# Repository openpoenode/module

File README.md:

# Technical Specifications

## Core Components

| Component              |                                  |
|------------------------|----------------------------------|
| MCU                    | ESP32-D0WD-V3                    |
| Flash                  | Winbond SPI 128MBit W25Q128JVP   |
| RAM                    | APMemory 64MBit APS6404L-3SQR-SN |
| Ethernet PHY           | SMSC LAN8720A                    |
| PoE 802.3af Controller | TI TPS23753                      |
| eFuse                  | TI TPS259520DSGR                 |

### Flash Memory

Any standard, pin-compatible SPI NOR flash in a WSON-8 6x5 mm package can be used. Common options are the 32MBit and 64MBit chips from the same line of Winbond flash memories.

### PSRAM

Installing a PSRAM chip is optional, the module will work just fine without the PSRAM IC populated. While any pin-compatible PSRAM chip can be installed, any amount over 32Mbit cannot be addressed by the ESP32 MCU.

### eFuse

- The digital power domain (MCU power supply input) is protected by a latch-off type eFuse. It disconnects supply at V<sub>in</sub> > 3.8V or I<sub>in</sub> > 1.04A.
- The module exposes a test pad for measuring the supply current drawn by the module's digital domain components:
  - I<sub>in</sub> = 1.81 x V<sub>test</sub>
  - V<sub>test</sub> is measured against digital ground

## Goldfinger Connector

The module exposes several signals of its components through a goldfinger connector:

### GPIOs

| GPIO | free | limited | input-only |
|------|------|---------|------------|
| 2    |      | X       |            |
| 4    |      | X       |            |
| 5    |      | X       |            |
| 12   |      | X       |            |
| 13   | X    |         |            |
| 14   | X    |         |            |
| 15   |      | X       |            |
| 18   | X    |         |            |
| 23   | X    |         |            |
| 32   | X    |         |            |
| 33   | X    |         |            |
| 34   |      |         | X          |
| 35   |      |         | X          |
| 36   |      |         | X          |
| 37   |      |         | X          |
| 38   |      |         | X          |
| 39   |      |         | X          |

GPIOs marked as "limited" have a boot-strapping function and/or a fixed pull-up/pull-down in place.

3 output-capable GPIOs have to be assigned for Ethernet PHY control.

### Ethernet Interface

- Analog (2 differential data pairs, 2x center taps power input)
- 2 Indicator LEDs (Link/Activity, Speed)
- Bob-Smith-Termination
- Digital interface (Enable/Reset, MDC, MDIO)

### Power Supply / Conversion

- High Voltage (PoE domain)
  - External power adapter input, 36V < V<sub>in</sub> < 54V
  - Direct PoE power output for additional DC/DC converters (maximum power draw limited to 802.3af level)
- Low Voltage (Isolated domain)
  - DC/DC converter V<sub>out</sub> = 5V (3.3V optional)
  - I<sub>out,max</sub> = 1.4A (5V) or 2.1A (3.3V)
  - 7W max. output
- Digital domain
  - MCU power supply input (external 3.3V supply required)
  - I<sub>supply,avg</sub> < 500mA (soft limit)
  - I<sub>supply,lim</sub> = 1.04A (latch-off limit)
  - I<sub>supply,idle</sub> = ~150mA (idle supply current - including flash, RAM, 100MBit connected Ethernet, Link/Speed indicators on)

### Programming Interface

- ESP32 UART
- MCU Reset
- GPIO0 (boot strapping only, no direct connection)

## Physical

- Standard Mini-PCIe goldfinger connector, 52 pins
- FR4 1.00 mm base material, 6 layers
- Size: 45 x 30 x 14.5 mm
- Weight: 12g

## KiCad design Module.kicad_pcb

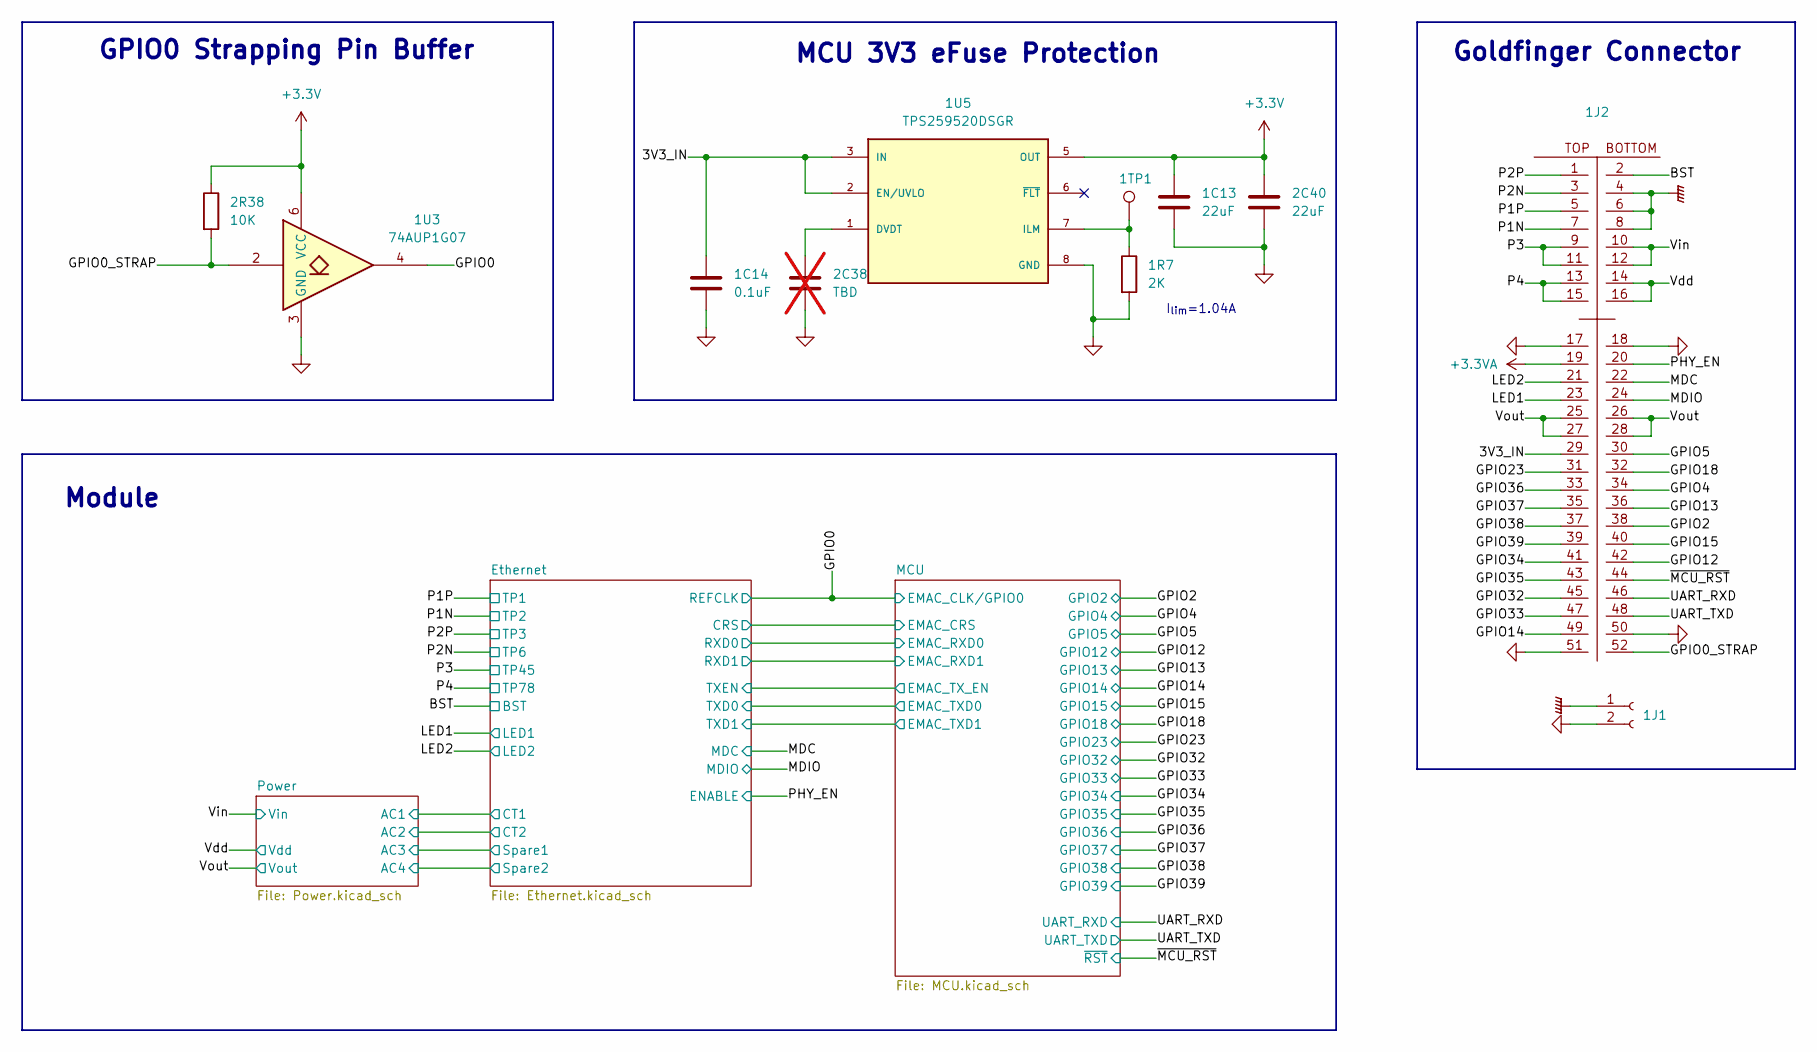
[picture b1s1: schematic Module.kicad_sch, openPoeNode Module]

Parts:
1C13, 2C40: 22uF; C_0805_2012Metric; MOUSER# 81-GRM21BZ71A226ME5L
1C14: 0.1uF; C_0402_1005Metric; MOUSER# 81-GCM155R71H104KE2J
1J1: HOLDDOWN; mPCIe-Hold
1J2: Mini-PCIe
1R7: 2K; R_0402_1005Metric; MOUSER# 71-CRCW0402-2.0K-E3
1TP1: TestPoint; TestPoint_Pad_D2.0mm
1U3: 74AUP1G07; Texas_USON-6_1x1.45mm_P0.5mm_SMD; MOUSER# 595-SN74AUP1G07DRYR
1U5: TPS259520DSGR; SON50P200X200X80-9N; MOUSER# 595-TPS259520DSGR
2C38: TBD; C_0402_1005Metric; not fitted
2R38: 10K; R_0402_1005Metric; MOUSER# 603-RE0402FRE0710KL

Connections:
+3.3V: 1C13.1, 1U3.6 (VCC), 1U5.5 (OUT), 2C40.1, 2R38.1; also elsewhere on the board
+3.3VA: 1J2.19; also elsewhere on the board
/3V3_IN: 1C14.2, 1J2.29, 1U5.2 (EN/UVLO), 1U5.3 (IN), 1U5.4 (IN)
/BST: 1J2.2; also elsewhere on the board
/GPIO0: 1U3.4; also elsewhere on the board
/GPIO0_STRAP: 1J2.52, 1U3.2, 2R38.2
/GPIO2: 1J2.38; also elsewhere on the board
/GPIO4: 1J2.34; also elsewhere on the board
/GPIO5: 1J2.30; also elsewhere on the board
/GPIO12: 1J2.42; also elsewhere on the board
/GPIO13: 1J2.36; also elsewhere on the board
/GPIO14: 1J2.49; also elsewhere on the board
/GPIO15: 1J2.40; also elsewhere on the board
/GPIO18: 1J2.32; also elsewhere on the board
/GPIO23: 1J2.31; also elsewhere on the board
/GPIO32: 1J2.45; also elsewhere on the board
/GPIO33: 1J2.47; also elsewhere on the board
/GPIO34: 1J2.41; also elsewhere on the board
/GPIO35: 1J2.43; also elsewhere on the board
/GPIO36: 1J2.33; also elsewhere on the board
/GPIO37: 1J2.35; also elsewhere on the board
/GPIO38: 1J2.37; also elsewhere on the board
/GPIO39: 1J2.39; also elsewhere on the board
/LED1: 1J2.23; also elsewhere on the board
/LED2: 1J2.21; also elsewhere on the board
/MDC: 1J2.22; also elsewhere on the board
/MDIO: 1J2.24; also elsewhere on the board
/P1N: 1J2.7; also elsewhere on the board
/P1P: 1J2.5; also elsewhere on the board
/P2N: 1J2.3; also elsewhere on the board
/P2P: 1J2.1; also elsewhere on the board
/P3: 1J2.9, 1J2.11; also elsewhere on the board
/P4: 1J2.13, 1J2.15; also elsewhere on the board
/PHY_EN: 1J2.20; also elsewhere on the board
/UART_RXD: 1J2.46; also elsewhere on the board
/UART_TXD: 1J2.48; also elsewhere on the board
/Vdd: 1J2.14, 1J2.16; also elsewhere on the board
/Vin: 1J2.10, 1J2.12; also elsewhere on the board
/Vout: 1J2.25, 1J2.26, 1J2.27, 1J2.28; also elsewhere on the board
/~MCU_RST: 1J2.44; also elsewhere on the board
GND: 1C13.2, 1C14.1, 1J1.2, 1J2.17, 1J2.18, 1J2.50, 1J2.51, 1R7.2, 1U3.3 (GND), 1U5.8 (GND), 1U5.9 (GND), 2C38.2, 2C40.2; also elsewhere on the board
GNDPWR: 1J1.1, 1J2.4, 1J2.6, 1J2.8; also elsewhere on the board
unnamed: 1U5.1 (DVDT), 2C38.1
unnamed: 1R7.1, 1TP1.1, 1U5.7 (ILM)

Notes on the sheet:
Goldfinger Connector
I_{lim}=1.04A
MCU 3V3 eFuse Protection
GPIO0 Strapping Pin Buffer
Module

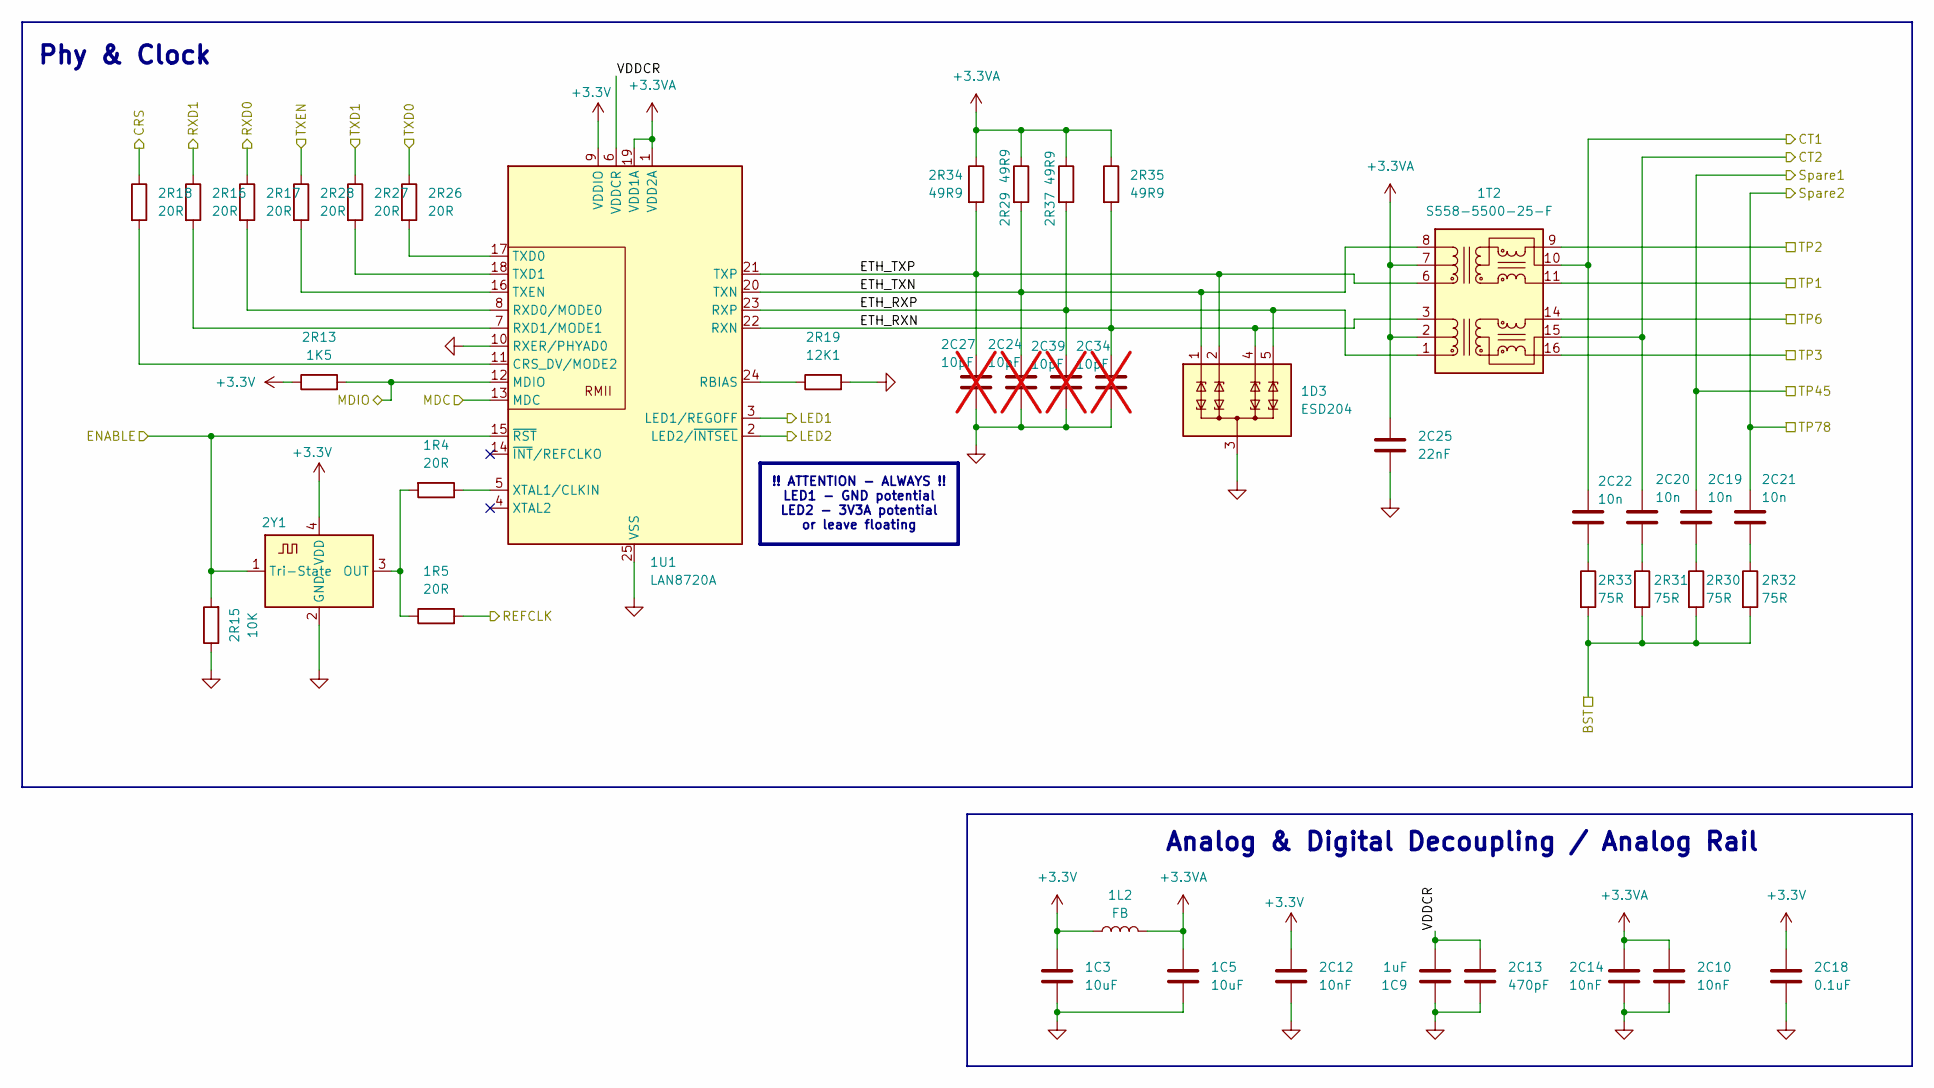
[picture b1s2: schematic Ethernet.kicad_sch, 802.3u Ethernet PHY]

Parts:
1C3, 1C5: 10uF; C_0805_2012Metric; MOUSER# 81-GRM21BR71A106MA3L
1C9: 1uF; C_0603_1608Metric; MOUSER# 963-EMK107B7105KA-T
1D3: ESD204; USON-10_2.5x1.0mm_P0.5mm; MOUSER# 595-ESD204DQAR
1L2: FB; L_0805_2012Metric; MOUSER#(alt) 603-BBPY201209121Y00
1R4, 1R5, 2R16, 2R17, 2R18, 2R26, 2R27, 2R28: 20R; R_0402_1005Metric; MOUSER# 660-RK73B1ETTP200J
1T2: S558-5500-25-F; MOUSER# 530-S558-5500-25-F
1U1: LAN8720A; QFN-24-1EP_4x4mm_P0.5mm_EP2.5x2.5mm; MOUSER# 579-LAN8720ACPTRABC
2C10, 2C12, 2C14: 10nF; C_0402_1005Metric; MOUSER# 963-EMK105B7103KV-F
2C13: 470pF; C_0402_1005Metric; MOUSER# 791-0402B471K250CT
2C18: 0.1uF; C_0402_1005Metric; MOUSER# 81-GCM155R71H104KE2J
2C19, 2C20, 2C21, 2C22: 10n; C_0603_1608Metric; MOUSER# 603-CC0603JRX70BB103
2C24, 2C27, 2C34, 2C39: 10pF; C_0402_1005Metric; MOUSER# 963-UMK105CG100DV-F; not fitted
2C25: 22nF; C_0402_1005Metric; MOUSER# 81-GRM155R71H223KA2J
2R13: 1K5; R_0402_1005Metric; MOUSER# 667-ERJ-2RKF1501X
2R15: 10K; R_0402_1005Metric; MOUSER# 603-RE0402FRE0710KL
2R19: 12K1; R_0402_1005Metric; MOUSER# 603-RT0402FRE0712K1L
2R29, 2R34, 2R35, 2R37: 49R9; R_0402_1005Metric; MOUSER# 660-RK73H1ETTP49R9F
2R30, 2R31, 2R32, 2R33: 75R; R_0603_1608Metric; MOUSER# 660-SG73S1JTTD75R0F
2Y1: ECS-2333-500-BN-TR; Crystal_SMD_3225-4Pin_3.2x2.5mm; MOUSER# 520-ECS-2333-500-BNT

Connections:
+3.3V: 1C3.1, 1L2.1, 1U1.9 (VDDIO), 2C12.2, 2C18.2, 2R13.1, 2Y1.4 (VDD); also elsewhere on the board
+3.3VA: 1C5.1, 1L2.2, 1T2.2 (C_TD), 1T2.7 (C_RD), 1U1.1 (VDD2A), 1U1.19 (VDD1A), 2C10.2, 2C14.2, 2C25.1, 2R29.1, 2R34.1, 2R35.1, 2R37.1; also elsewhere on the board
/BST: 2R30.2, 2R31.2, 2R32.2, 2R33.2; also elsewhere on the board
/Ethernet/CRS: 2R18.1; also elsewhere on the board
/Ethernet/CT1: 1T2.10 (C_RX), 2C22.1; also elsewhere on the board
/Ethernet/CT2: 1T2.15 (C_TX), 2C20.1; also elsewhere on the board
/Ethernet/ETH_RXN: 1D3.4 (TVS3), 1D3.7 (TVS3), 1T2.3 (TD-), 1U1.22 (RXN), 2C34.1, 2R35.2
/Ethernet/ETH_RXP: 1D3.5 (TVS4), 1D3.6 (TVS4), 1T2.1 (TD+), 1U1.23 (RXP), 2C39.1, 2R37.2
/Ethernet/ETH_TXN: 1D3.1 (TVS1), 1D3.10 (TVS1), 1T2.8 (RD-), 1U1.20 (TXN), 2C24.1, 2R29.2
/Ethernet/ETH_TXP: 1D3.2 (TVS2), 1D3.9 (TVS2), 1T2.6 (RD+), 1U1.21 (TXP), 2C27.1, 2R34.2
/Ethernet/RXD0: 2R17.1; also elsewhere on the board
/Ethernet/RXD1: 2R16.1; also elsewhere on the board
/Ethernet/TXD0: 2R26.1; also elsewhere on the board
/Ethernet/TXD1: 2R27.1; also elsewhere on the board
/Ethernet/TXEN: 2R28.1; also elsewhere on the board
/Ethernet/VDDCR: 1C9.1, 1U1.6 (VDDCR), 2C13.1
/GPIO0: 1R5.2; also elsewhere on the board
/LED1: 1U1.3 (LED1/REGOFF); also elsewhere on the board
/LED2: 1U1.2 (LED2/~INTSEL); also elsewhere on the board
/MDC: 1U1.13 (MDC); also elsewhere on the board
/MDIO: 1U1.12 (MDIO), 2R13.2; also elsewhere on the board
/P1N: 1T2.9 (RX-); also elsewhere on the board
/P1P: 1T2.11 (RX+); also elsewhere on the board
/P2N: 1T2.14 (TX-); also elsewhere on the board
/P2P: 1T2.16 (TX+); also elsewhere on the board
/P3: 2C19.1; also elsewhere on the board
/P4: 2C21.1; also elsewhere on the board
/PHY_EN: 1U1.15 (~RST), 2R15.2, 2Y1.1 (Tri-State); also elsewhere on the board
GND: 1C3.2, 1C5.2, 1C9.2, 1D3.3 (COM), 1D3.8 (COM), 1U1.10 (RXER/PHYAD0), 1U1.25 (VSS), 2C10.1, 2C12.1, 2C13.2, 2C14.1, 2C18.1, 2C24.2, 2C25.2, 2C27.2, 2C34.2, 2C39.2, 2R15.1, 2R19.2, 2Y1.2 (GND); also elsewhere on the board
unnamed: 1U1.11 (CRS_DV/MODE2), 2R18.2
unnamed: 1U1.24 (RBIAS), 2R19.1
unnamed: 1U1.8 (RXD0/MODE0), 2R17.2
unnamed: 1U1.7 (RXD1/MODE1), 2R16.2
unnamed: 1U1.17 (TXD0), 2R26.2
unnamed: 1U1.18 (TXD1), 2R27.2
unnamed: 1U1.16 (TXEN), 2R28.2
unnamed: 1R4.1, 1U1.5 (XTAL1/CLKIN)
unnamed: 2C19.2, 2R30.1
unnamed: 2C20.2, 2R31.1
unnamed: 2C21.2, 2R32.1
unnamed: 2C22.2, 2R33.1
unnamed: 1R4.2, 1R5.1, 2Y1.3 (OUT)

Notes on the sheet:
Phy & Clock
!! ATTENTION - ALWAYS !! LED1 - GND potential LED2 - 3V3A potential or leave floating
Analog & Digital Decoupling / Analog Rail

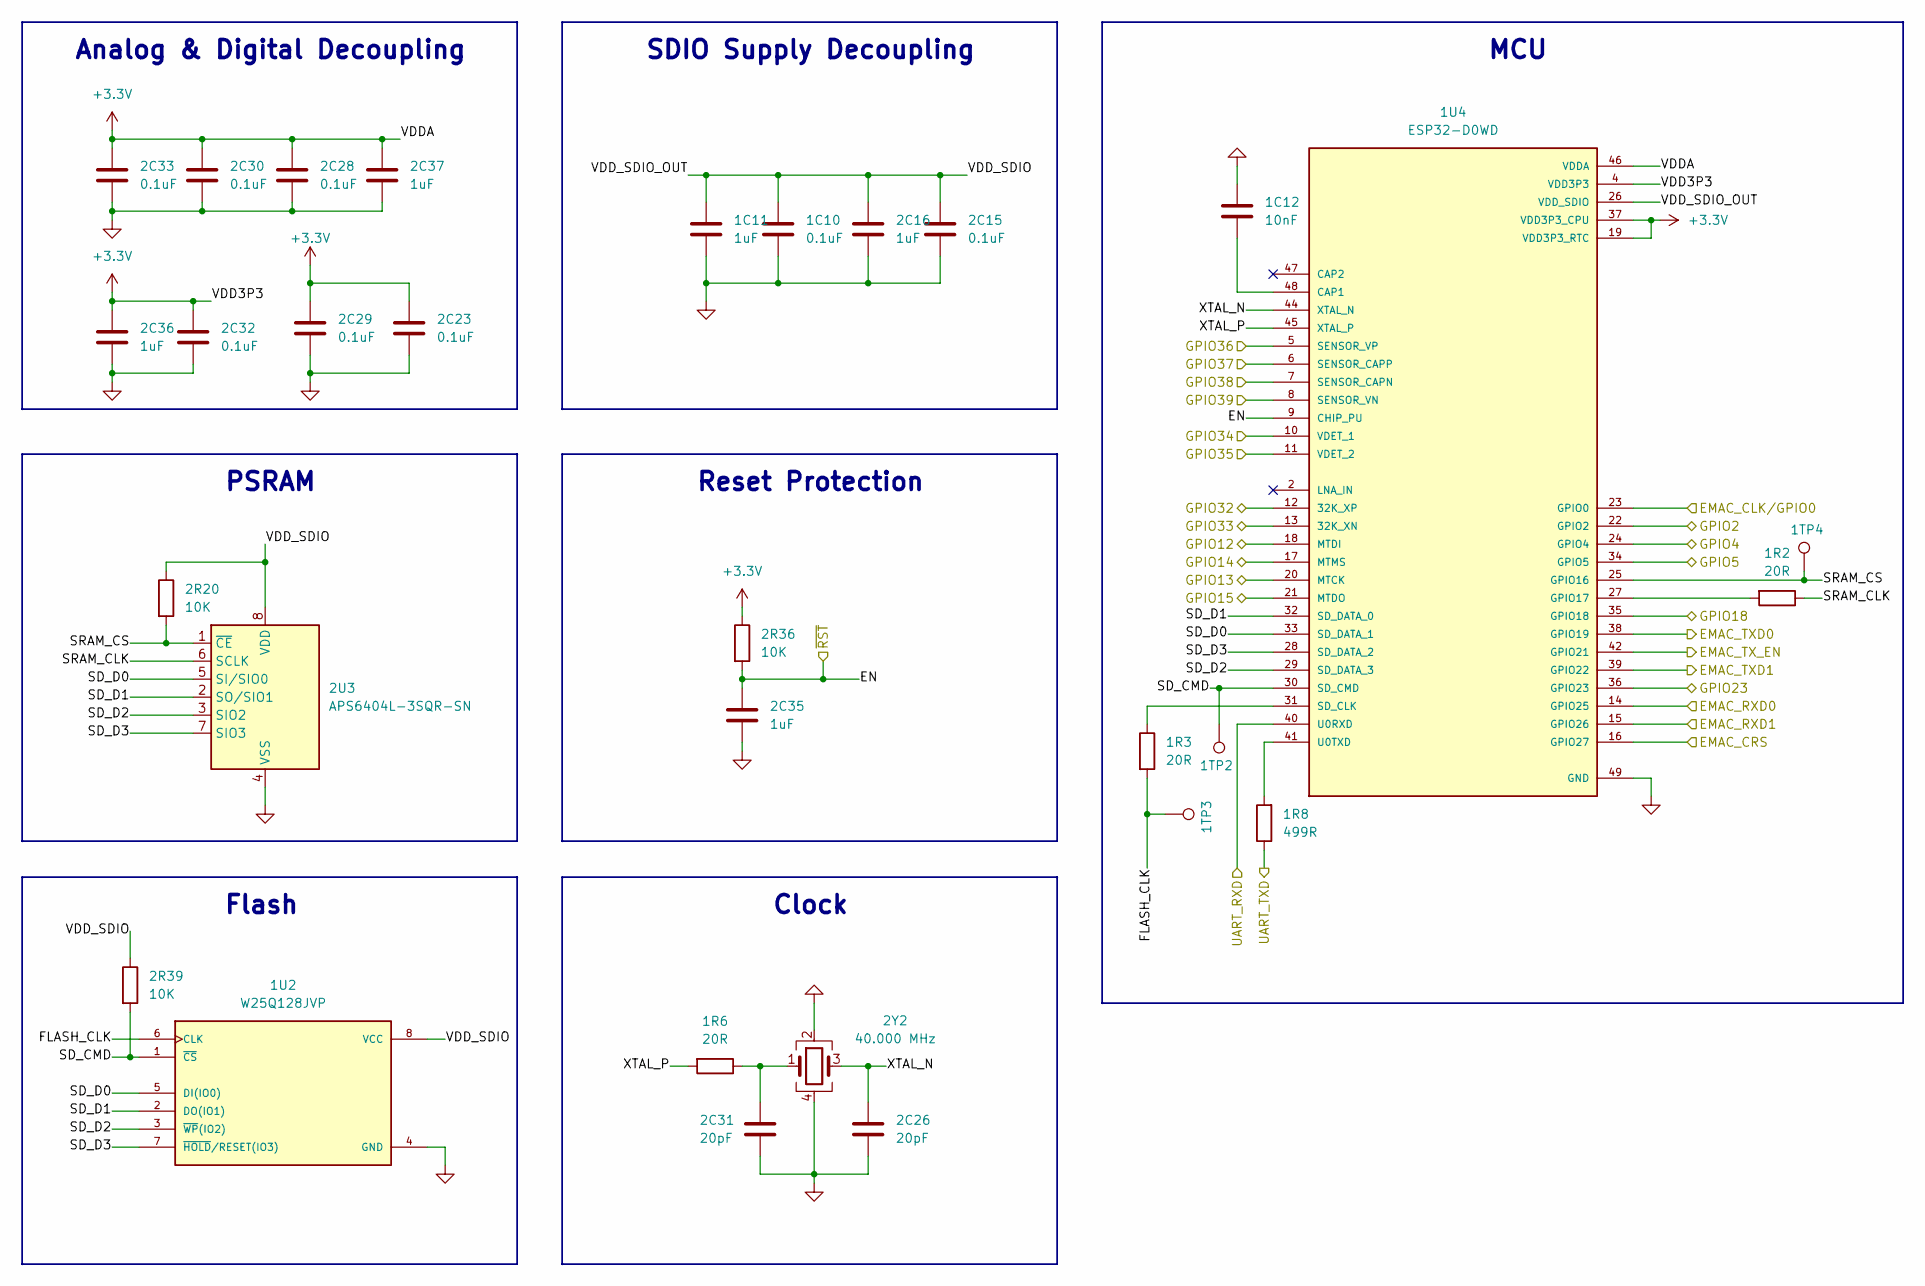
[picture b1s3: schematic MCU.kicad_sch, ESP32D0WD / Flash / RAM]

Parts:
1C10, 2C15, 2C23, 2C28, 2C29, 2C30, 2C32, 2C33: 0.1uF; C_0402_1005Metric; MOUSER# 81-GCM155R71H104KE2J
1C11, 2C16, 2C35, 2C36, 2C37: 1uF; C_0603_1608Metric; MOUSER# 963-EMK107B7105KA-T
1C12: 10nF; C_0402_1005Metric; MOUSER# 963-EMK105B7103KV-F
1R2, 1R3, 1R6: 20R; R_0402_1005Metric; MOUSER# 660-RK73B1ETTP200J
1R8: 499R; R_0402_1005Metric; MOUSER# 791-RMC1/16SK4990FTH
1TP2, 1TP3, 1TP4: TestPoint; TestPoint_Pad_D1.0mm
1U2: W25Q128JVP; SON127P600X500X80-9N; MOUSER# 454-W25Q128JVPIM
1U4: ESP32-D0WD; QFN-48-1EP_5x5mm_P0.35mm_EP3.7x3.7mm; MOUSER# 356-ESP32-D0WD-V3
2C26, 2C31: 20pF; C_0402_1005Metric; MOUSER# 187-CL05C200JB51PNC
2R20, 2R36, 2R39: 10K; R_0402_1005Metric; MOUSER# 603-RE0402FRE0710KL
2U3: APS6404L-3SQR-SN; SOIC-8_3.9x4.9mm_P1.27mm; MOUSER# 878-APS6404L-3SQR-SN
2Y2: 40.000 MHz; Crystal_SMD_3225-4Pin_3.2x2.5mm; MOUSER# 815-M840000MHZ12B1UT

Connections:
+3.3V: 1U4.1 (VDDA), 1U4.3 (VDD3P3), 1U4.4 (VDD3P3), 1U4.19 (VDD3P3_RTC), 1U4.37 (VDD3P3_CPU), 1U4.43 (VDDA), 1U4.46 (VDDA), 2C23.2, 2C28.2, 2C29.2, 2C30.2, 2C32.2, 2C33.2, 2C36.2, 2C37.2, 2R36.1; also elsewhere on the board
/Ethernet/CRS: 1U4.16 (GPIO27); also elsewhere on the board
/Ethernet/RXD0: 1U4.14 (GPIO25); also elsewhere on the board
/Ethernet/RXD1: 1U4.15 (GPIO26); also elsewhere on the board
/Ethernet/TXD0: 1U4.38 (GPIO19); also elsewhere on the board
/Ethernet/TXD1: 1U4.39 (GPIO22); also elsewhere on the board
/Ethernet/TXEN: 1U4.42 (GPIO21); also elsewhere on the board
/GPIO0: 1U4.23 (GPIO0); also elsewhere on the board
/GPIO2: 1U4.22 (GPIO2); also elsewhere on the board
/GPIO4: 1U4.24 (GPIO4); also elsewhere on the board
/GPIO5: 1U4.34 (GPIO5); also elsewhere on the board
/GPIO12: 1U4.18 (MTDI); also elsewhere on the board
/GPIO13: 1U4.20 (MTCK); also elsewhere on the board
/GPIO14: 1U4.17 (MTMS); also elsewhere on the board
/GPIO15: 1U4.21 (MTDO); also elsewhere on the board
/GPIO18: 1U4.35 (GPIO18); also elsewhere on the board
/GPIO23: 1U4.36 (GPIO23); also elsewhere on the board
/GPIO32: 1U4.12 (32K_XP); also elsewhere on the board
/GPIO33: 1U4.13 (32K_XN); also elsewhere on the board
/GPIO34: 1U4.10 (VDET_1); also elsewhere on the board
/GPIO35: 1U4.11 (VDET_2); also elsewhere on the board
/GPIO36: 1U4.5 (SENSOR_VP); also elsewhere on the board
/GPIO37: 1U4.6 (SENSOR_CAPP); also elsewhere on the board
/GPIO38: 1U4.7 (SENSOR_CAPN); also elsewhere on the board
/GPIO39: 1U4.8 (SENSOR_VN); also elsewhere on the board
/MCU/FLASH_CLK: 1R3.2, 1TP3.1, 1U2.6 (CLK)
/MCU/SD_CMD: 1TP2.1, 1U2.1 (~CS), 1U4.30 (SD_CMD), 2R39.2
/MCU/SD_D0: 1U2.5 (DI(IO0)), 1U4.33 (SD_DATA_1), 2U3.5 (SI/SIO0)
/MCU/SD_D1: 1U2.2 (DO(IO1)), 1U4.32 (SD_DATA_0), 2U3.2 (SO/SIO1)
/MCU/SD_D2: 1U2.3 (~WP(IO2)), 1U4.29 (SD_DATA_3), 2U3.3 (SIO2)
/MCU/SD_D3: 1U2.7 (~HOLD/RESET(IO3)), 1U4.28 (SD_DATA_2), 2U3.7 (SIO3)
/MCU/SRAM_CLK: 1R2.1, 2U3.6 (SCLK)
/MCU/SRAM_CS: 1TP4.1, 1U4.25 (GPIO16), 2R20.2, 2U3.1 (~CE)
/MCU/VDD_SDIO: 1C10.2, 1C11.2, 1U2.8 (VCC), 1U4.26 (VDD_SDIO), 2C15.2, 2C16.2, 2R20.1, 2R39.1, 2U3.8 (VDD)
/MCU/XTAL_N: 1U4.44 (XTAL_N), 2C26.1, 2Y2.3
/MCU/XTAL_P: 1R6.2, 1U4.45 (XTAL_P)
/UART_RXD: 1U4.40 (U0RXD); also elsewhere on the board
/UART_TXD: 1R8.1; also elsewhere on the board
/~MCU_RST: 1U4.9 (CHIP_PU), 2C35.2, 2R36.2; also elsewhere on the board
GND: 1C10.1, 1C11.1, 1C12.2, 1U2.4 (GND), 1U4.49 (GND), 2C15.1, 2C16.1, 2C23.1, 2C26.2, 2C28.1, 2C29.1, 2C30.1, 2C31.2, 2C32.1, 2C33.1, 2C35.1, 2C36.1, 2C37.1, 2U3.4 (VSS), 2Y2.2, 2Y2.4; also elsewhere on the board
unnamed: 1R6.1, 2C31.1, 2Y2.1
unnamed: 1C12.1, 1U4.48 (CAP1)
unnamed: 1R2.2, 1U4.27 (GPIO17)
unnamed: 1R3.1, 1U4.31 (SD_CLK)
unnamed: 1R8.2, 1U4.41 (U0TXD)

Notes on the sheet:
Flash
Reset Protection
MCU
Analog & Digital Decoupling
PSRAM
SDIO Supply Decoupling
Clock

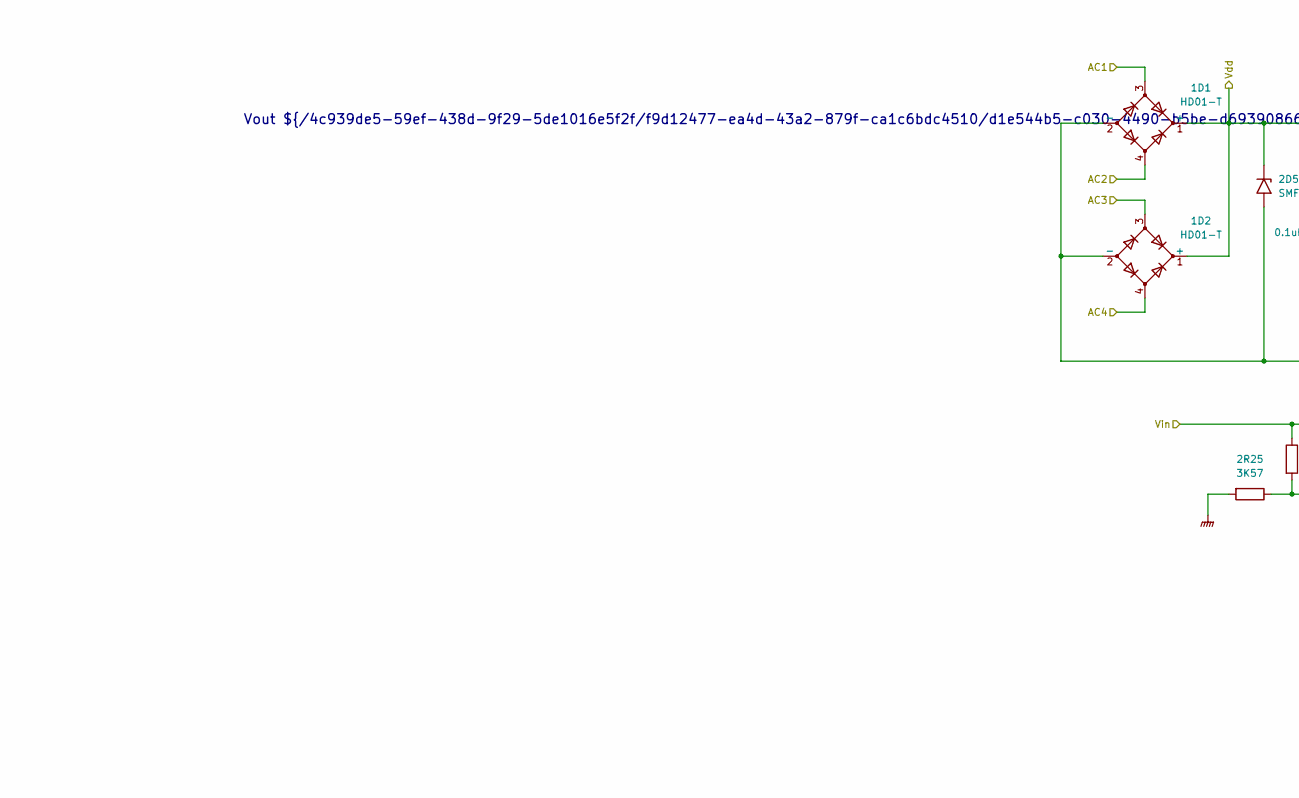
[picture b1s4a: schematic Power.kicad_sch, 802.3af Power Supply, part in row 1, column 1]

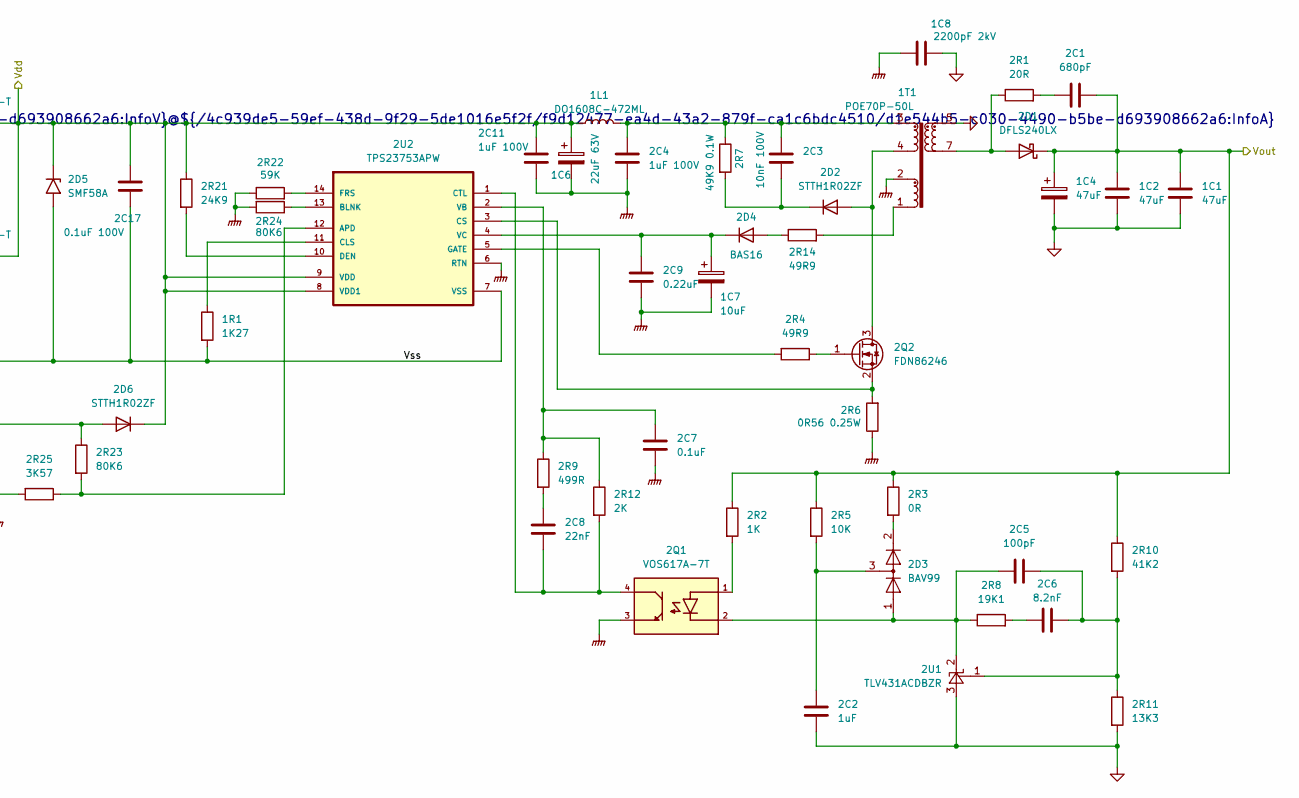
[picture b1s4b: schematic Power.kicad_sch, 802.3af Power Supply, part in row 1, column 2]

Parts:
1C1, 1C2: 47uF; C_1210_3225Metric; MOUSER# 187-CL32B476MPJNNNE
1C4: 47uF; CP_Elec_4x5.8; MOUSER# 667-EEE-FK0J470UR
1C6: 22uF 63V; CP_Elec_6.3x7.7; MOUSER# 667-EEE-FK1J220XP
1C7: 10uF; CP_Elec_4x5.8; MOUSER# 667-EEE-FK1E100R
1C8: 2200pF 2kV; C_1206_3216Metric; MOUSER# 581-1206GC222KAT2A
1D1, 1D2: HD01-T; SO_MiniDipHD01_4P9X4_DIO; MOUSER# 621-HD01-T
1L1: DO1608C-472ML; DO1608C; MOUSER# 994-DO1608C-472MLC
1R1: 1K27; R_0402_1005Metric; MOUSER# 603-RC0402FR-071K27L
1T1: POE70P-50L; POE3070P; MOUSER# 994-POE70P-50LD
2C1: 680pF; C_0603_1608Metric; MOUSER# 581-06035C681K4Z2A
2C2: 1uF; C_0603_1608Metric; MOUSER# 963-EMK107B7105KA-T
2C3: 10nF 100V; C_0603_1608Metric; MOUSER# 581-06031C103K4T2A
2C4, 2C11: 1uF 100V; C_0805_2012Metric; MOUSER# 963-HMR212CC7105KG-T
2C5: 100pF; C_0402_1005Metric; MOUSER# 187-CL05C101JB5NNND
2C6: 8.2nF; C_0402_1005Metric; MOUSER# 81-GCM155R71H822KA5J
2C7: 0.1uF; C_0402_1005Metric; MOUSER# 81-GCM155R71H104KE2J
2C8: 22nF; C_0402_1005Metric; MOUSER# 81-GRM155R71H223KA2J
2C9: 0.22uF; C_0402_1005Metric; MOUSER# 963-TMK105B7224KV-FR
2C17: 0.1uF 100V; C_0805_2012Metric; MOUSER# 187-CL21B104KCFSFNG
2D1: DFLS240LX; D_PowerDI-123; MOUSER# 621-DFLS240LX-7
2D2, 2D6: STTH1R02ZF; D_SOD-123F; MOUSER# 511-STTH1R02ZF
2D3: BAV99; SOT-23; MOUSER# 637-BAV99
2D4: BAS16; SOT-23; MOUSER# 833-BAS16-TP
2D5: SMF58A; P37_SOD-123FL; MOUSER# 637-SMF58A
2Q1: VOS617A-7T; SSOP-4_4.4x2.6mm_P1.27mm; MOUSER# 78-VOS617A-7T
2Q2: FDN86246; SOT-23; MOUSER# 512-FDN86246
2R1: 20R; R_0402_1005Metric; MOUSER# 660-RK73B1ETTP200J
2R2: 1K; R_0402_1005Metric; MOUSER# 603-RC0402FR-131KL
2R3: 0R; R_0402_1005Metric; MOUSER#.Var 3.3V(DNP) 5V(791-RMC10JPTH)
2R4, 2R14: 49R9; R_0402_1005Metric; MOUSER# 660-RK73H1ETTP49R9F
2R5: 10K; R_0402_1005Metric; MOUSER# 603-RE0402FRE0710KL
2R6: 0R56 0.25W; R_0805_2012Metric; MOUSER# 652-CRL0805FWR560ELF
2R7: 49K9 0.1W; R_0402_1005Metric; MOUSER# 667-ERJ-2RKF4992X
2R8: 19K1; R_0402_1005Metric; MOUSER# 652-CR0402-FX1912GLF
2R9: 499R; R_0402_1005Metric; MOUSER# 791-RMC1/16SK4990FTH
2R10: 41K2; R_0402_1005Metric; MOUSER# 652-CR0402-FX4122GLF
2R11: 13K3; R_0402_1005Metric; MOUSER# 603-RC0402FR-0713K3P
2R12: 2K; R_0402_1005Metric; MOUSER# 71-CRCW0402-2.0K-E3
2R21: 24K9; R_0402_1005Metric; MOUSER# 708-RMCF0402FT24K9
2R22: 59K; R_0402_1005Metric; MOUSER# 603-RC0402FR-1359KL
2R23, 2R24: 80K6; R_0402_1005Metric; MOUSER# 71-CRCW0402-80.6K-E3
2R25: 3K57; R_0402_1005Metric; MOUSER# 652-CR0402-FX3571GLF
2U1: TLV431ACDBZR; SOT-23-3; MOUSER# 595-TLV431ACDBZR
2U2: TPS23753APW; SOP65P640X120-14N; MOUSER# 595-TPS23753APWR

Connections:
/Ethernet/CT1: 1D1.3; also elsewhere on the board
/Ethernet/CT2: 1D1.4; also elsewhere on the board
/P3: 1D2.3; also elsewhere on the board
/P4: 1D2.4; also elsewhere on the board
/Power/Vss: 1D1.2 (-), 1D2.2 (-), 1R1.2, 2C17.2, 2D5.2 (A2), 2U2.7 (VSS)
/Vdd: 1C6.1, 1D1.1 (+), 1D2.1 (+), 1L1.1, 2C11.1, 2C17.1, 2D5.1 (A1), 2D6.1 (K), 2R21.1, 2U2.8 (VDD1), 2U2.9 (VDD); also elsewhere on the board
/Vin: 2D6.2 (A), 2R23.1; also elsewhere on the board
/Vout: 1C1.1, 1C2.1, 1C4.1, 2C1.2, 2D1.1 (K), 2R2.1, 2R3.1, 2R5.1, 2R10.1; also elsewhere on the board
GND: 1C1.2, 1C2.2, 1C4.2, 1C8.2, 1T1.5, 1T1.6, 2C2.1, 2R11.2, 2U1.3 (A); also elsewhere on the board
GNDPWR: 1C6.2, 1C7.2, 1C8.1, 1T1.2, 2C4.2, 2C7.2, 2C9.2, 2C11.2, 2Q1.3, 2R6.1, 2R22.1, 2R24.2, 2R25.2, 2U2.6 (RTN); also elsewhere on the board
unnamed: 1L1.2, 1T1.3, 2C3.1, 2C4.1, 2R7.1
unnamed: 1T1.1, 2R14.2
unnamed: 2C1.1, 2R1.2
unnamed: 2C2.2, 2D3.3 (K), 2R5.2
unnamed: 2C6.1, 2R8.2
unnamed: 2C8.1, 2R9.2
unnamed: 1T1.7, 1T1.8, 2D1.2 (A), 2R1.1
unnamed: 1T1.4, 2D2.2 (A), 2Q2.3 (D)
unnamed: 2C3.2, 2D2.1 (K), 2R7.2
unnamed: 2D3.2 (A), 2R3.2
unnamed: 2D4.1 (A), 2R14.1
unnamed: 1C7.1, 2C9.1, 2D4.3 (K), 2U2.4 (VC)
unnamed: 2Q1.1, 2R2.2
unnamed: 2Q2.1 (G), 2R4.1
unnamed: 2Q2.2 (S), 2R6.2, 2U2.3 (CS)
unnamed: 2C5.2, 2C6.2, 2R10.2, 2R11.1, 2U1.1 (FB)
unnamed: 2C5.1, 2D3.1 (K), 2Q1.2, 2R8.1, 2U1.2 (K)
unnamed: 2R23.2, 2R25.1, 2U2.12 (APD)
unnamed: 2R24.1, 2U2.13 (BLNK)
unnamed: 1R1.1, 2U2.11 (CLS)
unnamed: 2C8.2, 2Q1.4, 2R12.2, 2U2.1 (CTL)
unnamed: 2R21.2, 2U2.10 (DEN)
unnamed: 2R22.2, 2U2.14 (FRS)
unnamed: 2R4.2, 2U2.5 (GATE)
unnamed: 2C7.1, 2R9.1, 2R12.1, 2U2.2 (VB)

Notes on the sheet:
Vout ${/4c939de5-59ef-438d-9f29-5de1016e5f2f/f9d12477-ea4d-43a2-879f-ca1c6bdc4510/d1e544b5-c030-4490-b5be-d693908662a6:InfoV}@${/4c939de5-59ef-438d-9f29-5de1016e5f2f/f9d12477-ea4d-43a2-879f-ca1c6bdc4510/d1e544b5-c030-4490-b5be-d693908662a6:InfoA}

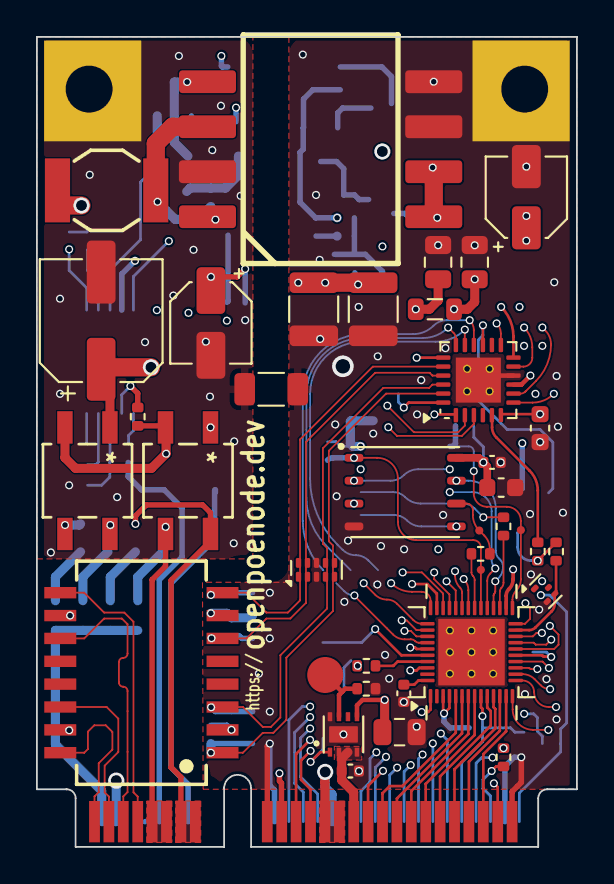
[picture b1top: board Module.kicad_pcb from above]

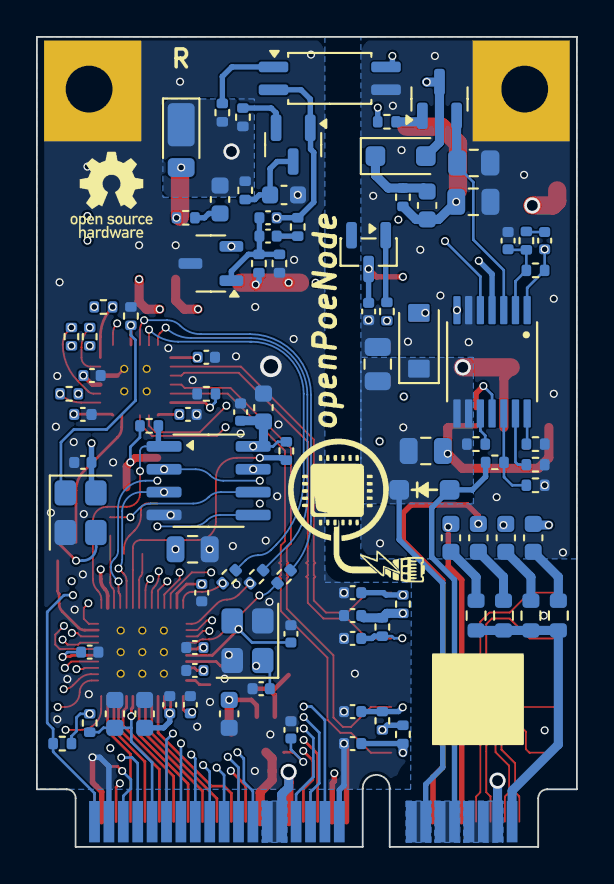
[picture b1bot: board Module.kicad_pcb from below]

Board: 6 copper layers, 30.0 x 45.0 mm, 132 parts (92 on the bottom side), 112 nets.

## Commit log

2026-01-09 moved serial number barcode away from via
2026-01-12 changed MOUSER# for R13 and arranged reference designators on PCB
2026-01-24 updated schematic headers
2026-01-25 updated Mouser part number for PSRAM
2026-01-26 all parts geo-renamed
2026-01-26 fixed PSRAM part value
2026-01-26 properties cleanup added unique parts ID
2026-01-29 fixed wrong flyback transformer pinout
2026-01-29 moved bottom 0402 resistors away from board edge
2026-01-29 increased trace width from all goldfinger connector traces to 6mil reduced mask and paste reduction of 1U3 to 1mil
2026-01-29 added testpoints to flash/ram signals
2026-01-29 moved three 0402 resistors away from board edge
2026-01-29 added test points for PoE stage
2026-01-31 fixed 2D4 polarity orientation and footprint
2026-01-31 fixed Flash and PSRAM to MCU pinout mapping added pull-up to Flash CS pin
2026-02-03 small, cosmetic fixes added project url to front silkscreen
2026-02-06 cosmetic changes
2026-02-20 ESP32 silk screen enhancement added missing part numbers finalized r0.3 work optimized Ethernet ESD diode position added second 22uF bulk updated transformer footprint courtyard enlarged supply curre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
2026-03-19 added IDAnything
2026-04-06 added some LCSC part numbers
2026-04-18 added README.md
2026-04-18 fixed image path
2026-04-23 added idle supply current info
